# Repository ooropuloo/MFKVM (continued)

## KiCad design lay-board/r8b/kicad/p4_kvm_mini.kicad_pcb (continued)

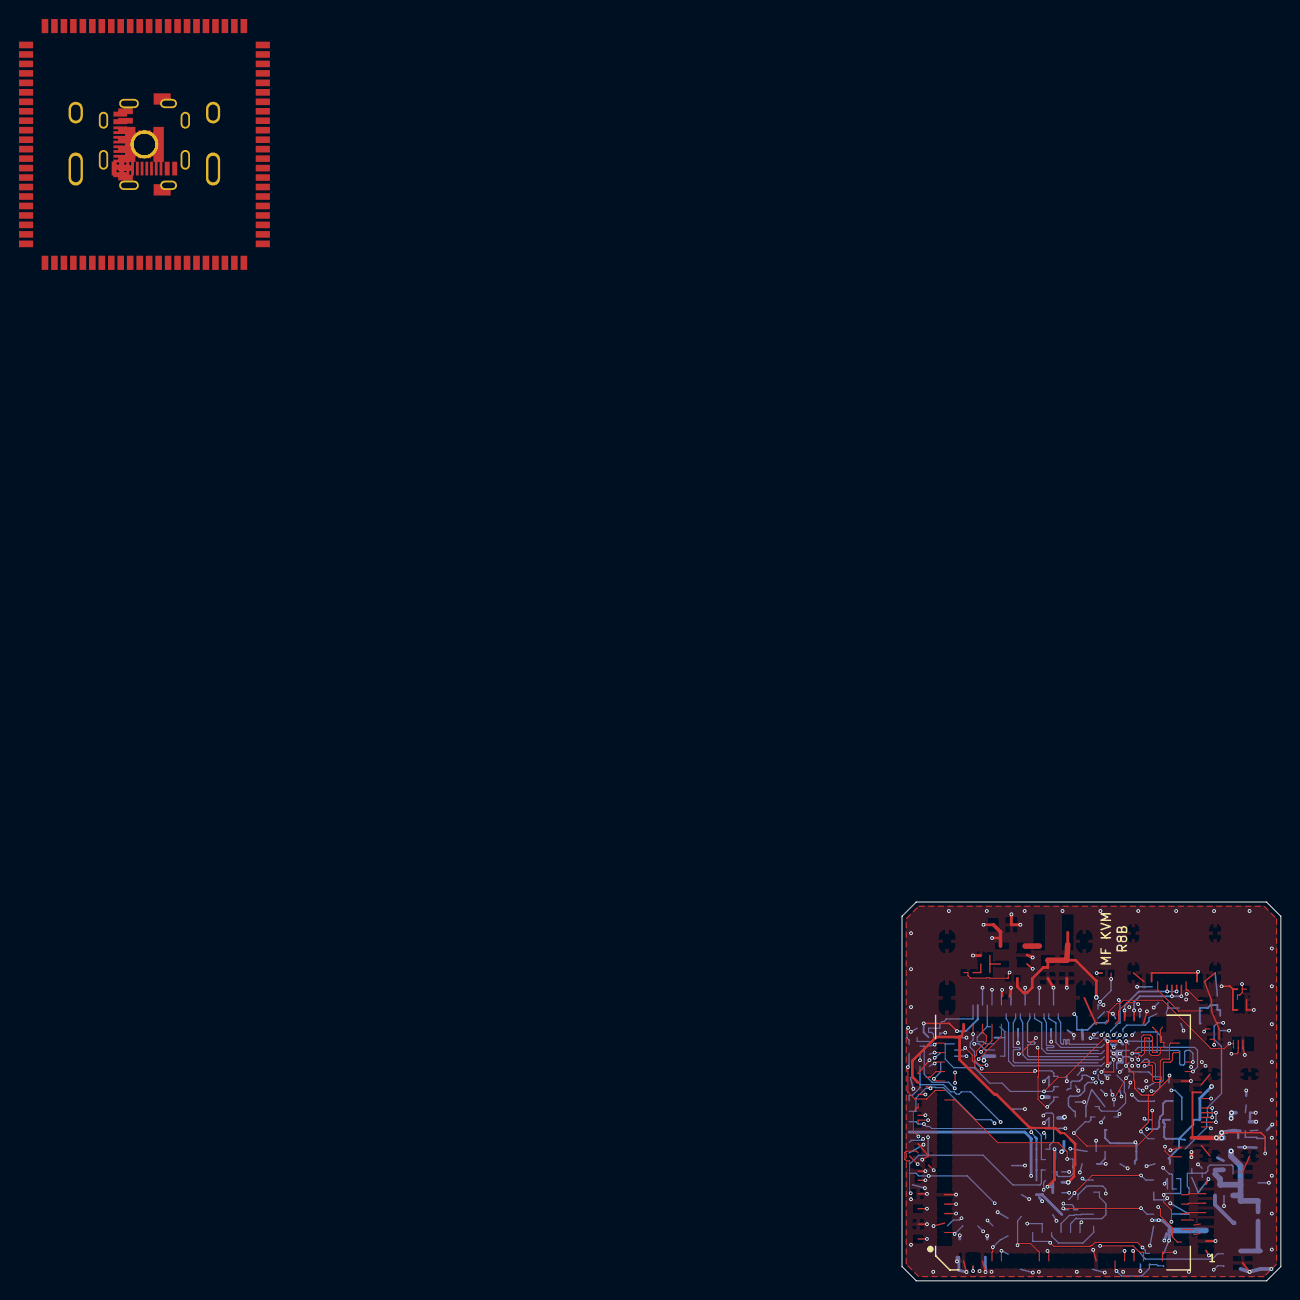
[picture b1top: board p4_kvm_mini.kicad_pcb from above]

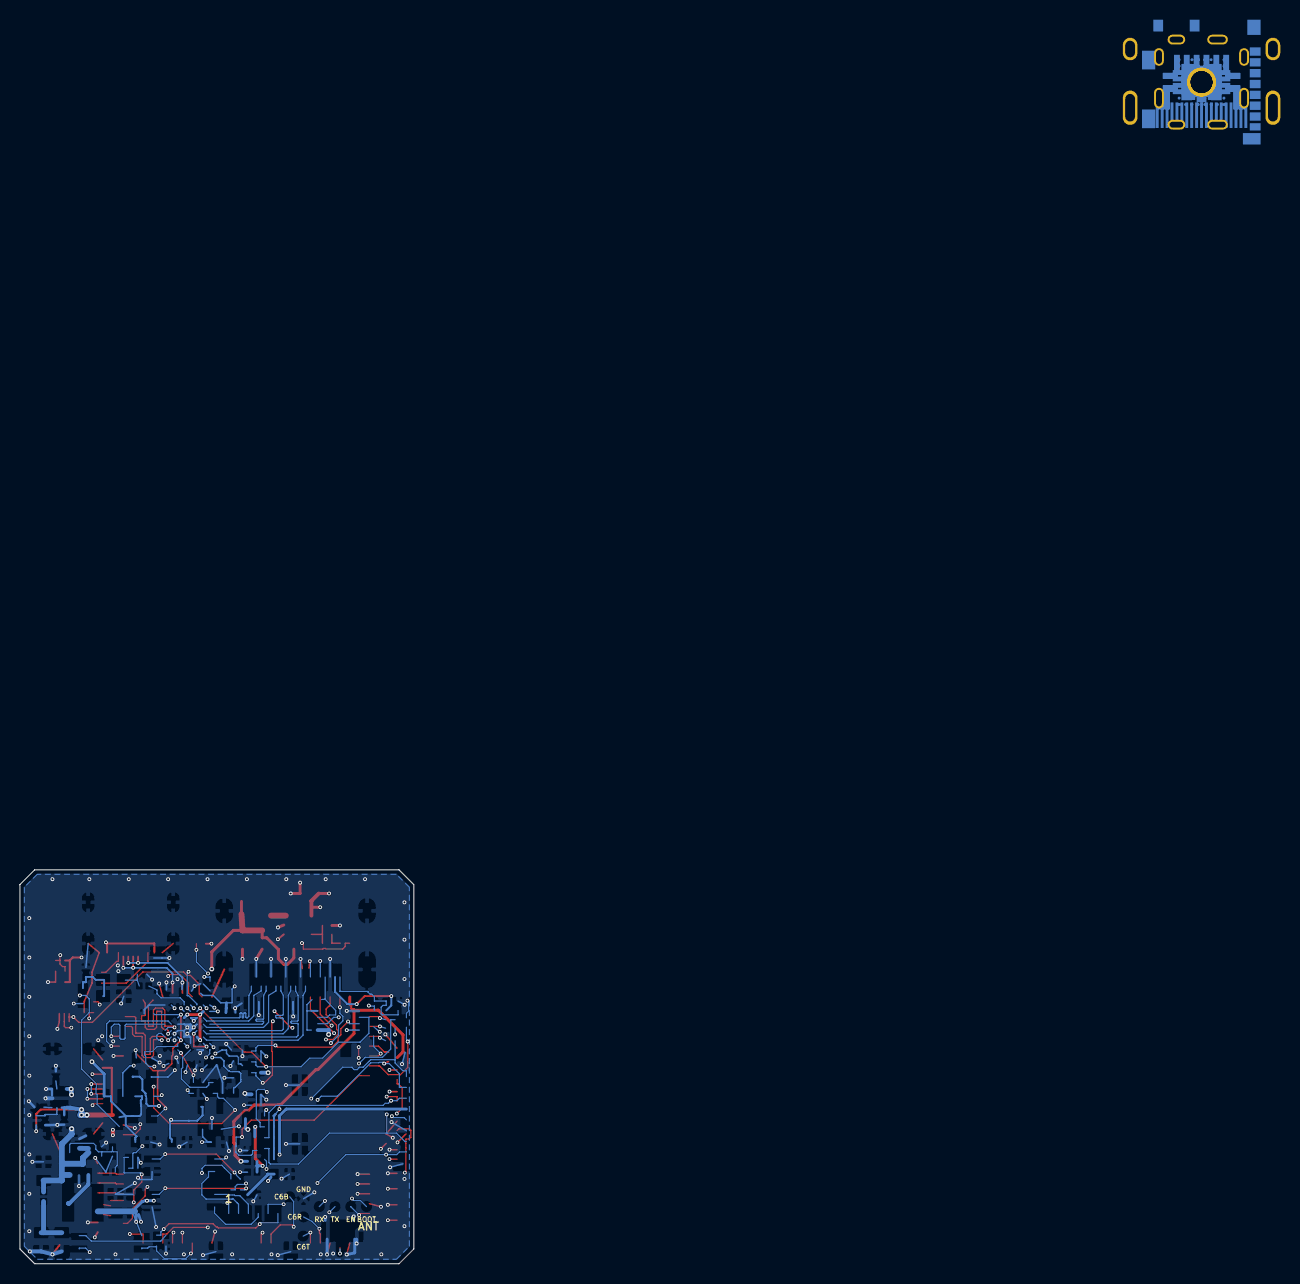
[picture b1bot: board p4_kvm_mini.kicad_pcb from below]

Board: 6 copper layers, 40.0 x 40.0 mm, 141 parts (102 on the bottom side), 108 nets.

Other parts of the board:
H1, H2, H3: MH plated GND; MH_2.2_PTH_GND

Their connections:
GND: H1.1, H2.1, H3.1; also elsewhere on the board

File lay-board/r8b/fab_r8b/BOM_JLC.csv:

Comment,Designator,Footprint,LCSC Part #
1k 0402,"R30,R73",R0402,C11702
33.2k 0402,R51,R0402,C122548
TPD4E05U06DQAR USB ESD,U3,USON-10,C138714
TPD4E05U06DQAR USB2 ESD,U14,USON-10,C138714
TPD4E05U06DQAR TMDS ESD,"U8,U9",USON-10,C138714
AO3401A,Q1,SOT-23,C15127
100nF 0402,"C21,C22,C23,C24,C25,C26,C27,C29,C3,C32,C33,C4,C41,C50,C6,C71",R0402,C1525
470pF 0402,"C13,C15,C17,C19",R0402,C1537
22pF 0402,"C63,C68",R0402,C1555
SM06B-SRSS-TB ATX,J4,JST_SM06B,C160405
SM08B-SRSS-TB round LCD,J6,JST_SM08B,C160407
0R 0402,"R42,R65",R0402,C17168
600R@100MHz,FB6,C0603,C19330
4.7uF 0603,"C14,C16,C18,C20",C0603,C19666
10uF 0603,"C1,C10,C11,C12,C2,C40",C0603,C19702
TCA9517ADGKR DDC level shift,U6,MSOP-8,C201698
TPS259531DSGR eFuse 5.7V clamp,U16,WSON-8_2x2_EP,C2155674
100 0402,R66,R0402,C25076
22 0402,"R24,R74,R75,R76,R77,R78,R79",R0402,C25092
270 0402,R54,R0402,C25099
470 0402,"R52,R53",R0402,C25117
100k 0402,"R32,R71,R9",R0402,C25741
10k 0402,"R11,R12,R13,R21,R25,R26,R27,R28,R40,R55",R0402,C25744
150k 0402,"R10,R50",R0402,C25755
47k 0402,R72,R0402,C25792
51k 0402,"R43,R44,R45,R46,R47,R67",R0402,C25794
2.2k 0402,"R22,R23",R0402,C25879
5.1k 0402,"R1,R2,R3,R4",R0402,C25905
1M 0402,R60,R0402,C26083
"TC358743XBG(EL,NOK",U7,BGA-64_6x6,C3008606
560 0.1% 0402,R62,R0402,C319512
33 0201,"R80,R81",R0201,C320843
2.2uF 0402,C70,R0402,C385032
2k 0402,R20,R0402,C4109
USB-C to host,J3,USB-C_HX_16P,C41427493
"USB-C 5V, flash and console",J5,USB-C_HX_16P,C41427493
0.47 0402,R68,R0402,C423162
22uF 0805,"C60,C61,C62,C65,C66,C67,C72,C73",C0805,C45783
TPD1E10B06DPYR CEC ESD,D1,X1SON-2_0.6x1,C48260
1uF 0402,"C5,C64",R0402,C52923
Molex 104031-0811 microSD,J7,microSD_Molex_104031-0811,C585350
HDMI-001S,J2,HDMI-001S,C720616
OT322527MJBA4SL 27MHz,Y1,OSC3225,C725995
33k 0.1% 0402,"R61,R63",R0402,C728559
SY8089AAAC 3.3V 2A,U2,SOT-23-5,C78988
SY8089AAAC 1.2V buck,U15,SOT-23-5,C78988
SWPA4020S2R2MT 2.2uH,"L1,L2",IND4020,C83423
220R@100MHz 2A BLM21PG221SN1D,"FB3,FB5",C0805,C85840
TLV73325PDBVR 2.5V,U4,SOT-23-5,C882825
U.FL-R-SMT-1(10) antenna,J8,U.FL-R-SMT-1,C88373
EL3H7(C)(TA)-G,"U10,U11,U12",SSOP-4_1.27,C92243
1k@100MHz 500mA,"FB2,FB4",C0805,C98485

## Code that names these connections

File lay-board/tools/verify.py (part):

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
# Waveshare wiki pin table, 2026-11-06, and the pinout picture agree. Only the pins this design uses are listed.
WIKI = {1: 'GND', 3: 'GND', 15: 'GND', 33: 'GND', 40: 'GND', 47: 'GND', 52: 'GND', 83: 'GND', 84: 'VBAT', 85: 'ESP_3V3', 86: 'ESP_3V3', 87: 'ESP_EN', 66: 'ESP_LDO_VO4',
        41: 'CSI_DATAN0', 42: 'CSI_DATAP0', 43: 'CSI_CLKP', 44: 'CSI_CLKN', 45: 'CSI_DATAN1', 46: 'CSI_DATAP1', 48: 'USB_DM', 49: 'USB_DP', 50: 'GPIO24', 51: 'GPIO25',
        62: 'GPIO35', 63: 'GPIO36', 64: 'GPIO37', 65: 'GPIO38', 67: 'GPIO39', 68: 'GPIO40', 69: 'GPIO41', 70: 'GPIO42', 71: 'GPIO43', 72: 'GPIO44', 73: 'GPIO45',
        22: 'GPIO7', 23: 'GPIO8', 32: 'GPIO23', 24: 'GPIO9', 25: 'GPIO10', 26: 'GPIO11', 27: 'GPIO12', 28: 'GPIO13', 17: 'GPIO2', 18: 'GPIO3', 19: 'GPIO4', 20: 'GPIO5', 4: 'C6_U0RXD', 5: 'C6_U0TXD', 9: 'C6_IO9', 10: 'C6_IO8'}
ROLE = {'GND': 'GND', 'VBAT': '3V3', 'ESP_3V3': '3V3', 'ESP_EN': 'ESP_EN', 'ESP_LDO_VO4': 'LDO_VO4',
        'CSI_DATAN0': 'CSI_D0_N', 'CSI_DATAP0': 'CSI_D0_P', 'CSI_CLKP': 'CSI_CK_P', 'CSI_CLKN': 'CSI_CK_N', 'CSI_DATAN1': 'CSI_D1_N', 'CSI_DATAP1': 'CSI_D1_P',
        'USB_DM': 'USB_DN', 'USB_DP': 'USB_DP', 'GPIO24': 'USB2_DN', 'GPIO25': 'USB2_DP', 'GPIO35': 'BOOT', 'GPIO36': 'GPIO36', 'GPIO37': 'U0_TX', 'GPIO38': 'U0_RX',
        'GPIO39': 'SD_D0', 'GPIO40': 'SD_D1', 'GPIO41': 'SD_D2', 'GPIO42': 'SD_D3', 'GPIO43': 'SD_CLK', 'GPIO44': 'SD_CMD', 'GPIO45': 'SD_PWR_N',
        'GPIO7': 'I2C_SDA', 'GPIO8': 'I2C_SCL', 'GPIO23': 'TC_RST', 'GPIO9': 'LCD_DIN', 'GPIO10': 'LCD_CLK', 'GPIO11': 'LCD_CS', 'GPIO12': 'LCD_DC', 'GPIO13': 'LCD_RST',
        'GPIO2': 'ATX_LED', 'GPIO3': 'HOST_VBUS_DIV', 'GPIO4': 'ATX_PWR', 'GPIO5': 'ATX_RST', 'C6_U0RXD': 'C6_RXD', 'C6_U0TXD': 'C6_TXD', 'C6_IO9': 'C6_IO9', 'C6_IO8': 'C6_IO8'}
bad = {k: (ROLE[v], pads.get(f'U1.{k}')) for k, v in WIKI.items() if pads.get(f'U1.{k}') != ROLE[v]}
check(not bad, f'{len(WIKI)} module pins match the vendor pin table {bad or ""}')

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        count[n].append(k)
single = {n: v for n, v in count.items() if len(v) < 2}
ok_single = {'C6_IO8x'}
check(not {n for n in single if n not in ok_single and not n.startswith(('GPIO36',))}, f'no net has only one pin {single or ""}')

# every stocked part number must actually be the stated value; read from JLC's listing into stock.json
stock = {r[0]: r for r in json.load(open(f'{OUT}/stock.json', encoding='utf-8'))}
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
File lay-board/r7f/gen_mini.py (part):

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          4: 'C6_RXD', 5: 'C6_TXD', 9: 'C6_IO9', 10: 'C6_IO8',
          41: 'CSI_D0_N', 42: 'CSI_D0_P', 43: 'CSI_CK_P', 44: 'CSI_CK_N', 45: 'CSI_D1_N', 46: 'CSI_D1_P',
          48: 'USB_DN', 49: 'USB_DP', 50: 'USB2_DN', 51: 'USB2_DP',
          62: 'BOOT', 63: 'GPIO36', 64: 'U0_TX', 65: 'U0_RX',
          67: 'SD_D0', 68: 'SD_D1', 69: 'SD_D2', 70: 'SD_D3', 71: 'SD_CLK', 72: 'SD_CMD', 73: 'SD_PWR_N',
          22: 'I2C_SDA', 23: 'I2C_SCL', 32: 'TC_RST',
          24: 'LCD_DIN', 25: 'LCD_CLK', 26: 'LCD_CS', 27: 'LCD_DC', 28: 'LCD_RST',
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C('C4', '100n', -18.3, 8.9, 90, '3V3', 'GND', 'F')
R('R11', '10k', -19.2, 7.3, 90, 'ESP_EN', '3V3', 'F')
C('C5', '1u', -18.3, 6.0, 90, 'ESP_EN', 'GND', 'F')  # F5: 10k + 1 uF, Espressif guideline v1.9
R('R12', '10k', -18.3, 3.0, 90, 'GPIO36', '3V3', 'F')
R('R13', '10k', -18.3, 0.8, 90, 'C6_IO8', '3V3', 'F')
C('C6', '100n', -18.3, -1.4, 90, 'LDO_VO4', 'GND', 'F')

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C('C40', '10u', -6.6, 10.9, 0, 'SD1_VDD')
C('C41', '100n', -3.6, 13.0, 0, 'SD1_VDD')
for i, net in enumerate(('SD_D2', 'SD_D3', 'SD_CMD', 'SD_D0', 'SD_D1')):
    R(f'R{43 + i}', '51k', -5.32, 5.0 + i * 1.1, 0, net, 'LDO_VO4')  # F1: pull-ups on the IO supply, so 3V3 cannot back-feed the pins before VO4 is up

# ---------- power
C('C60', '22u', 17.6, 10.6, 90, '5V')
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r6_add('FB_1V2', 'F', [(-10.72, -13.45), (-9.6, -13.45)], 0.15)                   # to U15.5 FB
r6_add('FB_MID', 'F', [(-11.68, -13.45), (-11.68, -12.55), (-12.52, -12.55)], 0.15)
R7_RAILW = [('V1V2', 'F', [(-2.5, -15.5), (-2.6, -13.85)], 0.6), ('V1V2', 'F', [(-2.6, -13.85), (-4.6, -13.85)], 0.6)]
# item 1: U6.5 (EN) to U6.8 (VCCB, 5V) on B, outside the pin row between U6 and U9 (0.55 mm). The DDC_SDA branch to R28 used that gap
# (R7_DROP_BOX); R28 moves to just above U6, between this 5V line and the DDC_SDA line to J2.16. Every way through a via was blocked: see R7_REPORT.md
R7_RAILW += [('5V', 'B', [(-9.67, -6.75), (-9.15, -6.23), (-9.15, -3.725), (-9.6, -3.725)], 0.127), ('5V', 'B', [(-9.6, -5.675), (-9.15, -5.675)], 0.127),
             ('DDC_SDA', 'B', [(-10.63, -6.75), (-11.0, -6.782)], 0.127)]   # R28 (DDC_SDA pull-up) moved here: its old branch ran through that gap
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       'meta': {'filename': f'{NAME}.kicad_pro', 'version': 3}}
json.dump(pro, open(f'{OUT}/{NAME}.kicad_pro', 'w'), indent=1)
# r6: nothing runs beside the antenna line. Pours keep this gap too, which is the gap its width was solved for.
open(f'{OUT}/{NAME}.kicad_dru', 'w', newline='\n').write('(version 1)\n(rule "LNA_OUT clearance"\n  (layer outer)\n  (condition "A.NetName == \'LNA_OUT\'")\n  (constraint clearance (min 0.25mm)))\n'
                                                     # r7c: JLC "Pad hole-to-hole spacing 0.45mm", applied to a pad hole (PTH, slot, NPTH) against any hole, vias included.
                                                     # Via to via stays at the board rule, 0.2 mm (JLC "Via-to-via hole spacing").
                                                     '(rule "component hole to any hole"\n  (condition "A.Type == \'Pad\' || B.Type == \'Pad\'")\n  (constraint hole_to_hole (min 0.45mm)))\n')
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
